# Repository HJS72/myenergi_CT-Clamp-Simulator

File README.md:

# Myenergi CT Clamp Simulator

ESP32-based simulator for Myenergi CT clamp inputs with support for standalone, master and slave operation.

## Deutsch

Kurze Projektzusammenfassung:

- Simuliert 3-phasige CT-Signale fur Harvi/Zappi-ahnliche Eingange
- MQTT-Eingang fur `PhaseA_Amp`, `PhaseB_Amp`, `PhaseC_Amp` und `SumPower_kW`
- Stromwerte sind bipolar: `-CURRENT_MAX` bis `+CURRENT_MAX` (Standard: -100A..+100A)
- Webserver auf dem Master mit WiFi- und MQTT-Konfiguration, Live-Graph und OTA
- Optionales OLED-Display fur kompakte Laufzeitanzeige
- Master-Slave-Betrieb uber UART fur Phase B und C

## Wichtige MQTT-Topics

Standardpfad:

```text
/esp32CTSimulator/PhaseA_Amp
/esp32CTSimulator/PhaseB_Amp
/esp32CTSimulator/PhaseC_Amp
/esp32CTSimulator/SumPower_kW
/esp32CTSimulator/Status
```

## Build

```bash
cd myenergi_CT-Clamp-Simulator

.venv/bin/pio run -e esp32
.venv/bin/pio run -e esp32-master
.venv/bin/pio run -e esp32-slave
```

## Flashen

```bash
.venv/bin/pio run -e esp32-master -t upload
```

## Hinweis zu den Display-Testdateien in `src`

- `src/display_test_main.cpp` und `src/display_test_u8g2_main.cpp` sind optionale Diagnoseprogramme fur OLED-Tests.
- Sie werden von der normalen Firmware nicht mitgebaut.
- Sie werden nur uber die separaten PlatformIO-Umgebungen `esp32-display-test` und `esp32-display-test-u8g2` verwendet.
- Wenn du keine separaten OLED-Hardwaretests mehr brauchst, kann man sie entfernen.
- Solange du eine einfache Display-Diagnose im Repo behalten willst, sind sie sinnvoll.

## Dokumentation

- Details zum aktuellen Release: [docs/README.md](docs/README.md)
- Schnellstart: [docs/QUICKSTART.md](docs/QUICKSTART.md)
- MQTT-Schnittstelle: [docs/MQTT.md](docs/MQTT.md)
- Master-Slave-Setup: [docs/MASTER_SLAVE_QUICKSTART.md](docs/MASTER_SLAVE_QUICKSTART.md)
- Hardware und Verdrahtung: [docs/HARDWARE.md](docs/HARDWARE.md)
- PCB-Unterlagen: [hardware/pcb/master_slave/README.md](hardware/pcb/master_slave/README.md)

## English

Short project summary:

- Simulates 3-phase CT clamp signals for Harvi/Zappi-like inputs
- MQTT input for `PhaseA_Amp`, `PhaseB_Amp`, `PhaseC_Amp`, and `SumPower_kW`
- Current values are bipolar: `-CURRENT_MAX` to `+CURRENT_MAX` (default: -100A..+100A)
- Master web server with WiFi and MQTT configuration, live graph, and OTA
- Optional OLED display for compact runtime status
- Master-slave operation over UART for Phase B and Phase C

## Important MQTT Topics

Default path:

```text
/esp32CTSimulator/PhaseA_Amp
/esp32CTSimulator/PhaseB_Amp
/esp32CTSimulator/PhaseC_Amp
/esp32CTSimulator/SumPower_kW
/esp32CTSimulator/Status
```

## Build

```bash
cd myenergi_CT-Clamp-Simulator

.venv/bin/pio run -e esp32
.venv/bin/pio run -e esp32-master
.venv/bin/pio run -e esp32-slave
```

## Flash

```bash
.venv/bin/pio run -e esp32-master -t upload
```

## Note About The Display Test Files In `src`

- `src/display_test_main.cpp` and `src/display_test_u8g2_main.cpp` are optional OLED diagnostic programs.
- They are not built as part of the main firmware targets.
- They are only used by the dedicated PlatformIO environments `esp32-display-test` and `esp32-display-test-u8g2`.
- If you no longer need separate OLED hardware diagnostics, they can be removed.
- If you want to keep a simple display validation path in the repo, they are still useful.

## Documentation

- Current release details: [docs/README.md](docs/README.md)
- Quick start: [docs/QUICKSTART.md](docs/QUICKSTART.md)
- MQTT interface: [docs/MQTT.md](docs/MQTT.md)
- Master-slave setup: [docs/MASTER_SLAVE_QUICKSTART.md](docs/MASTER_SLAVE_QUICKSTART.md)
- Hardware and wiring: [docs/HARDWARE.md](docs/HARDWARE.md)
- PCB files: [hardware/pcb/master_slave/README.md](hardware/pcb/master_slave/README.md)

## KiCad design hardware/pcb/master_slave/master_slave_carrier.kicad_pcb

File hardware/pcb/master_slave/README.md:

# Master-Slave PCB (Carrier Board)

This folder contains a practical PCB starter package for the Master-Slave variant:
- One board hosts two ESP32 DevKitC V4 NodeMCU modules (Master + Slave)
- UART between modules is routed on-board
- Shared USB-C power input feeds both ESP32 modules
- Phase A/B/C analog outputs are exposed via three 2-pin terminal connectors (each phase + GND)
- Optional 1.3 inch OLED I2C display header for live 3-phase current display

## Files
- netlist.csv: Logical net connections
- bom.csv: PCB BOM (components and footprints)
- placement.csv: Suggested XY placement baseline
- fab_notes.md: Manufacturing and routing constraints
- DEVKITC_V4_PINMAP.md: Full 2x19 pin map and project node mapping

## Board concept
- Left socket: Master ESP32 DevKitC V4 NodeMCU (WiFi + MQTT + Phase A)
- Right socket: Slave ESP32 DevKitC V4 NodeMCU (Phase B + Phase C)
- Shared USB-C 5V input and common GND
- Output terminals to Harvi/Zappi:
	- J4A: Phase A / GND
	- J4B: Phase B / GND
	- J4C: Phase C / GND
- OLED connector:
	- J6-1: 3V3
	- J6-2: GND
	- J6-3: SCL (GPIO22)
	- J6-4: SDA (GPIO21)

## Recommended KiCad workflow
1. Create new KiCad project in this folder
2. Place footprints from bom.csv
3. Use placement.csv XY hints
4. Route nets from netlist.csv
5. Apply routing constraints from fab_notes.md
6. Run ERC/DRC
7. Export Gerber + Drill + BOM + CPL

## Expected firmware pin mapping
- Master GPIO25 -> Phase A
- Slave GPIO25 -> Phase C
- Slave GPIO26 -> Phase B
- Master GPIO17 -> Slave GPIO16
- Slave GPIO17 -> Master GPIO16
- Master GPIO32 -> Slave EN (serial pass-through OTA control)
- Master GPIO33 -> Slave GPIO0 (serial pass-through OTA boot control)

## Serial Pass-Through OTA Wiring

Required additional control wires for flashing the slave through the master web UI:

- `Master GPIO32` -> `Slave EN`
- `Master GPIO33` -> `Slave GPIO0`

Recommended implementation:

- Drive both control lines through NPN transistor stages or open-drain MOSFETs.
- Keep Slave EN pulled up (10k to 3V3).
- Keep Slave GPIO0 pulled up (10k to 3V3).
- Ensure Master and Slave share a low-impedance common ground.

The firmware uses these lines to reset the slave and force boot mode before UART image transfer.

## DAC Output Wiring (Production)

Use the following direct mapping from ESP32 DAC pins to output terminal blocks:

- Phase A (Master DAC)
	- Source: `J1A-9_IO25` (Master GPIO25 / DAC1)
	- Net: `PHASE_A_DAC`
	- Destination: `J4A-1` (Phase A output)
	- Return: `J4A-2` -> `GND`

- Phase B (Slave DAC)
	- Source: `J2A-10_IO26` (Slave GPIO26 / DAC2)
	- Net: `PHASE_B_DAC`
	- Destination: `J4B-1` (Phase B output)
	- Return: `J4B-2` -> `GND`

- Phase C (Slave DAC)
	- Source: `J2A-9_IO25` (Slave GPIO25 / DAC1)
	- Net: `PHASE_C_DAC`
	- Destination: `J4C-1` (Phase C output)
	- Return: `J4C-2` -> `GND`

Optional analog smoothing/filter per phase:

- Series resistor in output path:
	- `R1` on Phase A
	- `R2` on Phase B
	- `R3` on Phase C
- Shunt capacitor from phase net to GND:
	- `C1` on Phase A
	- `C2` on Phase B
	- `C3` on Phase C

This creates a simple RC low-pass per DAC channel and can reduce high-frequency DAC noise before the external interface stage.

## ESP32 Module Variant
- Target module: ESP32 DevKitC V4 NodeMCU (38-pin)
- Socket style: two rows of 1x19 pins at 2.54mm pitch
- Verify your exact board revision pin labels before final routing

## Header Numbering Used In Netlist
- `J1A/J2A`: left header row, pins 1..19 from USB side to opposite edge
- `J1B/J2B`: right header row, pins 1..19 from USB side to opposite edge
- Key references used:
	- `A-19_5V` for module 5V input
	- `B-1_GND` for module ground reference
	- `A-9_IO25` and `A-10_IO26` for DAC outputs
	- `B-11_IO17` and `B-12_IO16` for UART interconnect
	- `A-2_EN` for optional reset switch

## Notes
- This is a carrier-board style design for ESP32 DevKitC V4 NodeMCU modules
- No mains wiring on PCB
- Low-voltage signals only
- USB-C is used as power sink only (USB2.0 data lines not used)

## ASCII Wiring Schema (Production)

```text
Power entry and distribution
----------------------------
 USB-C J3
	VBUS ----> F1 (polyfuse) ----> 5V_IN ----> J1A-19 (Master 5V)
														+-> J2A-19 (Slave 5V)

	GND  ----------------------------------> J1B-1 (Master GND)
		+-----------------------------------> J2B-1 (Slave GND)

	CC1 ----> RCC1 5.1k ----> GND
	CC2 ----> RCC2 5.1k ----> GND

Master/Slave interconnect
-------------------------
 UART_TX_M2S:  J1B-11 (Master IO17 TX) ----> J2B-12 (Slave IO16 RX)
 UART_RX_S2M:  J2B-11 (Slave  IO17 TX) ----> J1B-12 (Master IO16 RX)
 SLAVE_EN_CTL: J1A-7  (Master IO32)    ----> J2A-2  (Slave EN)
 SLAVE_BOOT:   J1A-8  (Master IO33)    ----> J2B-14 (Slave IO0)
 Common GND:   J1B-1 -----------------------> J2B-1

OLED header J6 (optional)
-------------------------
 J6-1 (VCC) <---- J1A-1  (Master 3V3)
 J6-2 (GND) <---- J1B-1  (Master GND)
 J6-3 (SCL) <---- J1B-3  (Master IO22)
 J6-4 (SDA) <---- J1B-6  (Master IO21)

 Optional pull-ups:
	R4: J6-3 (SCL) -> J6-1 (3V3)
	R5: J6-4 (SDA) -> J6-1 (3V3)

Phase outputs to external terminal blocks
-----------------------------------------
 PHASE_A_DAC: J1A-9  (Master IO25) ----> J4A-1 (Phase A)
 PHASE_B_DAC: J2A-10 (Slave  IO26) ----> J4B-1 (Phase B)
 PHASE_C_DAC: J2A-9  (Slave  IO25) ----> J4C-1 (Phase C)

 Ground returns:
	J4A-2 -> GND
	J4B-2 -> GND
	J4C-2 -> GND

Optional enable/reset switches
------------------------------
 SW1-1 ----> J1A-2 (Master EN)
 SW2-1 ----> J2A-2 (Slave EN)
```

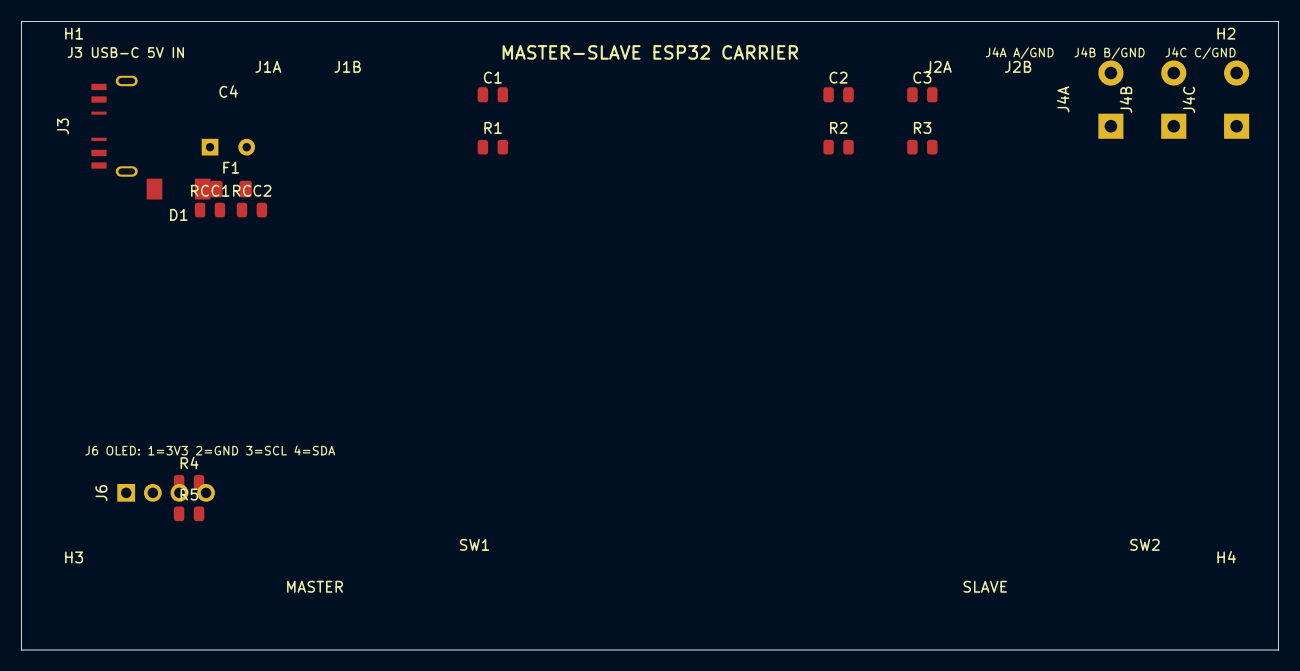
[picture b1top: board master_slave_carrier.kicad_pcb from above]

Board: 2 copper layers, 120.0 x 60.0 mm, 28 parts (0 on the bottom side), 10 nets, no tracks yet.

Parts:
C1, C2, C3: 100nF; C_0805_2012Metric
C4: 470uF; CP_Radial_D8.0mm_P3.50mm
D1: SS14; D_SMA
F1: PTC_1A; Fuse_1206_3216Metric
H1, H2, H3, H4: M3; MountingHole_3.2mm_M3
J1A: MASTER_LEFT_DEVKITC_V4; PinSocket_1x19_P2.54mm_Vertical
J1B: MASTER_RIGHT_DEVKITC_V4; PinSocket_1x19_P2.54mm_Vertical
J2A: SLAVE_LEFT_DEVKITC_V4; PinSocket_1x19_P2.54mm_Vertical
J2B: SLAVE_RIGHT_DEVKITC_V4; PinSocket_1x19_P2.54mm_Vertical
J3: USB_C_POWER; USB_C_Receptacle_HRO_TYPE-C-31-M-12
J4A: PHASE_A; TerminalBlock_Phoenix_MKDS-1,5-2_5.08mm
J4B: PHASE_B; TerminalBlock_Phoenix_MKDS-1,5-2_5.08mm
J4C: PHASE_C; TerminalBlock_Phoenix_MKDS-1,5-2_5.08mm
J6: OLED_I2C; PinHeader_1x04_P2.54mm_Vertical
R1, R2, R3: 10k; R_0805_2012Metric
R4, R5: 4.7k; R_0805_2012Metric
RCC1, RCC2: 5.1k; R_0805_2012Metric
SW1: MASTER_RESET; SW_PUSH_6mm
SW2: SLAVE_RESET; SW_PUSH_6mm

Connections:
5V_IN: C4.1, D1.1, D1.2, F1.1, F1.2, J3.A4, J3.B4
GND: C1.2, C2.2, C3.2, C4.2, J3.A1, J3.B1, J3.S1, J4A.2, J4B.2, J4C.2, J6.2, RCC1.2, RCC2.2
I2C_SCL: J6.3, R4.1
I2C_SDA: J6.4, R5.1
OLED_VCC: J6.1, R4.2, R5.2
PHASE_A_DAC: C1.1, J4A.1, R1.1, R1.2
PHASE_B_DAC: C2.1, J4B.1, R2.1, R2.2
PHASE_C_DAC: C3.1, J4C.1, R3.1, R3.2
USB_CC1: J3.A5, RCC1.1
USB_CC2: J3.B5, RCC2.1

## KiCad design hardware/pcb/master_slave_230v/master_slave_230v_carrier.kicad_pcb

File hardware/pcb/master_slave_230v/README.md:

# Master-Slave PCB (230VAC Input Variant)

This folder contains a second PCB variant with mains input and isolated 5V generation.

## Purpose
- One board hosts both ESP32 modules (Master + Slave)
- Board is powered from 230VAC using an isolated AC/DC module
- Same phase output mapping (A/B/C/GND) to Harvi/Zappi

## Files
- netlist.csv: Net-level connectivity
- bom.csv: Suggested BOM for 230VAC variant
- placement.csv: Suggested footprint placement
- fab_notes.md: Isolation and fabrication constraints
- master_slave_230v_carrier.kicad_pro: KiCad project file
- master_slave_230v_carrier.kicad_dru: Design rules incl. HV/LV constraints
- master_slave_230v_carrier.kicad_pcb: Board template with outline, connectors and keepout zone
- MANUFACTURER_NOTES.md: Ready-to-send fabrication and assembly notes

## Architecture
- Primary side (HV): AC input, fuse, MOV, NTC, AC/DC module input
- Isolation barrier: creepage/clearance + slot
- Secondary side (LV): 5V rail, ESP32 sockets, UART and analog outputs

## Output mapping
- Master GPIO25 -> Phase A
- Slave GPIO25 -> Phase B
- Slave GPIO26 -> Phase C
- J5A output terminal: Phase A / GND
- J5B output terminal: Phase B / GND
- J5C output terminal: Phase C / GND

## Important
This is a high-voltage design concept and requires qualified design verification before real deployment.

## Current board template status
- Board outline is defined (126mm x 66mm)
- HV/LV keepout barrier is defined (x=60..68mm)
- Main connectors and module sockets are pre-placed
- Silkscreen warnings for HV area are included
- Pre-routing added for critical power path (L_IN -> F1 -> NTC1 -> PS1, N_IN -> PS1)
- Pre-routing added for secondary path (PS1 -> F2 -> 5V_MAIN and GND_ISO distribution)
- Pre-routing added for output resistors to PHASE terminal block
- Signal matrix headers added:
	- J6 MASTER_SIG: GPIO25, TX, RX, GND nets
	- J7 SLAVE_SIG: GPIO25, GPIO26, RX, TX, GND nets
	- J8 MASTER_DEVKIT_BRIDGE: fixed bridge points to Master module
	- J9 SLAVE_DEVKIT_BRIDGE: fixed bridge points to Slave module
- Silkscreen pin legend added next to J8/J9 for direct assembly reference
- Additional silkscreen legends added for connectors:
	- J1: AC input pin order L/N/PE
	- J2: 5V service connector +5V/GND
	- J5A: Harvi/Zappi output pin order A/GND
	- J5B: Harvi/Zappi output pin order B/GND
	- J5C: Harvi/Zappi output pin order C/GND
	- Protection parts labels (F1, MOV1, NTC1, PS1, F2)

## Fixed bridge mapping (ESP32 DevKit V1 30-pin)
Wire these short bridges during assembly:

Master side:
- J8-1 -> Master GPIO25
- J8-2 -> Master GPIO17
- J8-3 -> Master GPIO16
- J8-4 -> Master GND

Slave side:
- J9-1 -> Slave GPIO25
- J9-2 -> Slave GPIO26
- J9-3 -> Slave GPIO16
- J9-4 -> Slave GPIO17
- J9-5 -> Slave GND

Before fabrication:
1. Verify/adjust footprints against your KiCad libraries
2. Finalize bridge routing from J6/J7 to the exact ESP32 socket pads used on your module revision
3. Run full DRC/ERC with project rules
4. Review creepage/clearance with your compliance target

## Gerber Preflight Checklist

Use this checklist before sending to a PCB manufacturer.

### 1. Electrical and rule checks
- [ ] ERC in schematic passes (no unresolved power pins)
- [ ] DRC in PCB passes with zero unapproved violations
- [ ] HV/LV barrier keepout remains intact (x=60..68mm)
- [ ] Minimum HV clearance/c creepage targets are met per `fab_notes.md`
- [ ] Net continuity checked for: L_IN, N_IN, 5V_MAIN, GND_ISO, UART_TX_M2S, UART_RX_S2M, PHASE_A/B/C

### 2. Safety-critical review
- [ ] Fuse F1 value/type verified for your application
- [ ] MOV1 voltage class verified (275VAC class for 230VAC systems)
- [ ] NTC1 inrush part verified (power rating and surge capability)
- [ ] AC/DC module pinout and footprint verified against datasheet
- [ ] No copper pour crosses isolation barrier
- [ ] HV markings and connector polarity labels are readable on silkscreen

### 3. Mechanical checks
- [ ] Board size and mounting holes fit enclosure
- [ ] USB connector access for both ESP32 modules is unobstructed
- [ ] Terminal block orientation supports wiring entry direction
- [ ] Component heights fit enclosure constraints

### 4. Fabrication outputs
Generate and verify these files:
- [ ] Gerber layers: F.Cu, B.Cu, F.Mask, B.Mask, F.SilkS, B.SilkS, Edge.Cuts
- [ ] Drill files (Excellon)
- [ ] Pick-and-place file (if assembly service is used)
- [ ] BOM export aligned with `bom.csv`
- [ ] Readme/notes for manufacturer mentioning isolation slot and HV spacing requirements

### 5. Visual review in Gerber viewer
- [ ] Edge.Cuts is a closed contour
- [ ] HV traces are not routed through keepout channel
- [ ] Terminal pin numbering matches silkscreen legends
- [ ] No accidental text overlap on pads/vias
- [ ] Mounting holes are free of copper where required

## Recommended KiCad Export Steps

1. Open `master_slave_230v_carrier.kicad_pro`.
2. Run `Inspect -> Design Rules Checker` and clear all critical issues.
3. Open `File -> Fabrication Outputs -> Gerbers` and select required layers.
4. Generate drill files via `File -> Fabrication Outputs -> Drill Files`.
5. Validate all outputs in KiCad Gerber Viewer or an external viewer.
6. Package Gerbers + drill + BOM + fabrication notes into a zip archive.

## First Power-Up Checklist (No ESP32 installed)

- [ ] Apply mains input via isolated bench setup and RCD-protected line
- [ ] Measure secondary output from AC/DC module: expected ~5V
- [ ] Verify no abnormal heating in F1/MOV1/NTC1/PS1
- [ ] Verify 5V_MAIN to GND_ISO is stable under light dummy load

After that:
- [ ] Install Master/Slave ESP32 modules
- [ ] Perform UART and DAC functional tests per `docs/TESTING.md`

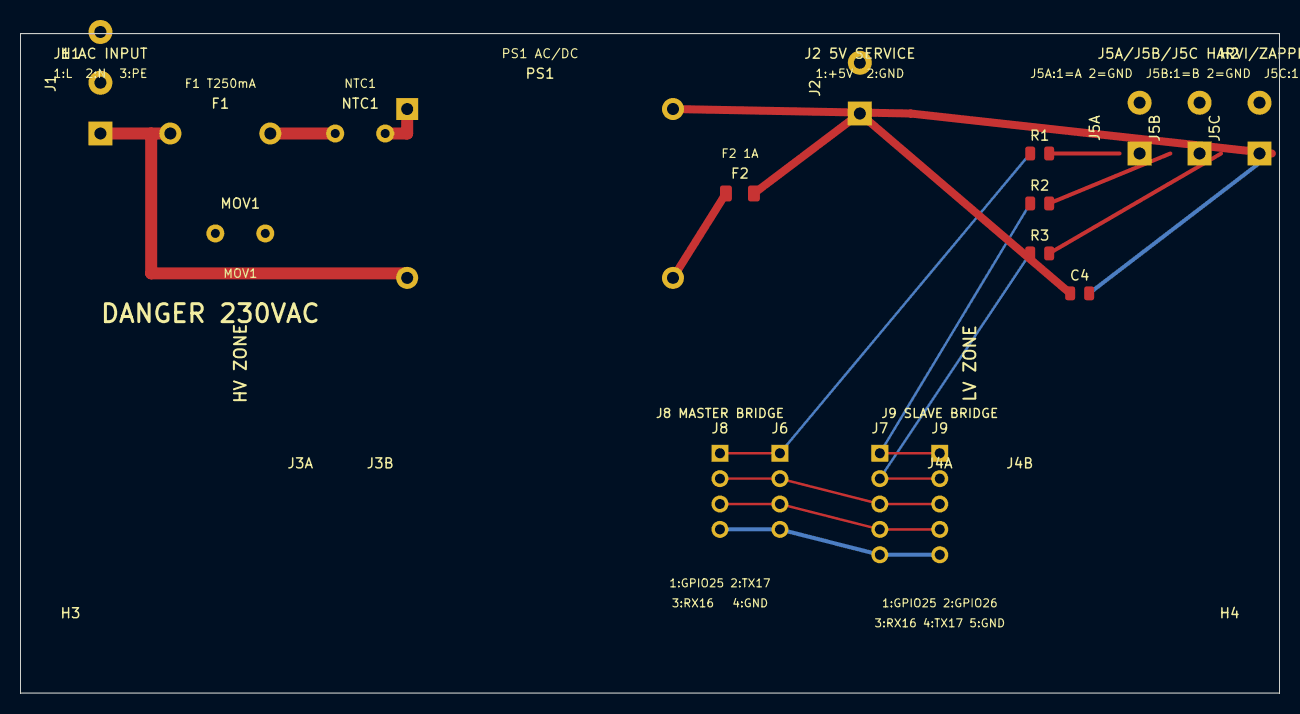
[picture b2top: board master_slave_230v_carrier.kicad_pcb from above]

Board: 2 copper layers, 126.0 x 66.0 mm, 26 parts (0 on the bottom side), 15 nets.

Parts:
C4: 100n; C_0805_2012Metric
F1: T250mA; Fuseholder_5x20mm
F2: PTC_1A; Fuse_1206_3216Metric
H1, H2, H3, H4: M3; MountingHole_3.2mm_M3
J1: AC_IN; TerminalBlock_Phoenix_MKDS-1,5-3_5.08mm
J2: 5V_SERVICE; TerminalBlock_Phoenix_MKDS-1,5-2_5.08mm
J3A: MASTER_L; PinSocket_1x19_P2.54mm_Vertical
J3B: MASTER_R; PinSocket_1x19_P2.54mm_Vertical
J4A: SLAVE_L; PinSocket_1x19_P2.54mm_Vertical
J4B: SLAVE_R; PinSocket_1x19_P2.54mm_Vertical
J5A: PHASE_A_OUT; TerminalBlock_Phoenix_MKDS-1,5-2_5.08mm
J5B: PHASE_B_OUT; TerminalBlock_Phoenix_MKDS-1,5-2_5.08mm
J5C: PHASE_C_OUT; TerminalBlock_Phoenix_MKDS-1,5-2_5.08mm
J6: MASTER_SIG; PinHeader_1x04_P2.54mm_Vertical
J7: SLAVE_SIG; PinHeader_1x05_P2.54mm_Vertical
J8: MASTER_DEVKIT_BRIDGE; PinHeader_1x04_P2.54mm_Vertical
J9: SLAVE_DEVKIT_BRIDGE; PinHeader_1x05_P2.54mm_Vertical
MOV1: 14D471K; RV_Disc_D9.0mm_W4.6mm_P5.0mm
NTC1: 10D-9; RV_Disc_D9.0mm_W4.6mm_P5.0mm
PS1: HLK-PM01; Converter_ACDC_HiLink_HLK-PMxx
R1, R2, R3: 10k; R_0805_2012Metric

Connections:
5V_ISO: F2.1, PS1.3
5V_MAIN: C4.1, F2.2, J2.1
GND_ISO: C4.2, J2.2, J5A.2, J5B.2, J5C.2, J6.4, J7.5, J8.4, J9.5, PS1.4
L_FUSED: F1.2, NTC1.1
L_IN: F1.1, J1.1
L_LIMITED: MOV1.1, NTC1.2, PS1.1
N_IN: J1.2, MOV1.2, PS1.2
PHASE_A_DAC: J6.1, J8.1, R1.1
PHASE_A_OUT: J5A.1, R1.2
PHASE_B_DAC: J7.1, J9.1, R2.1
PHASE_B_OUT: J5B.1, R2.2
PHASE_C_DAC: J7.2, J9.2, R3.1
PHASE_C_OUT: J5C.1, R3.2
UART_RX_S2M: J6.3, J7.4, J8.3, J9.4
UART_TX_M2S: J6.2, J7.3, J8.2, J9.3

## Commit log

2026-04-03 Initial commit: rename project to myenergi_CT-Clamp-Simulator and include master-slave PCB variants
2026-04-12 add display
    show values/graph
    fallback single mode
    -> Phase A = Sum
2026-04-17 Final beta version
2026-04-17 v1.0417.2114
2026-04-18 Gerber Export Files from KiKad
2026-04-18 code cleaning - first release
2026-04-20 add support for negative phases
    also add version information in Web-View
